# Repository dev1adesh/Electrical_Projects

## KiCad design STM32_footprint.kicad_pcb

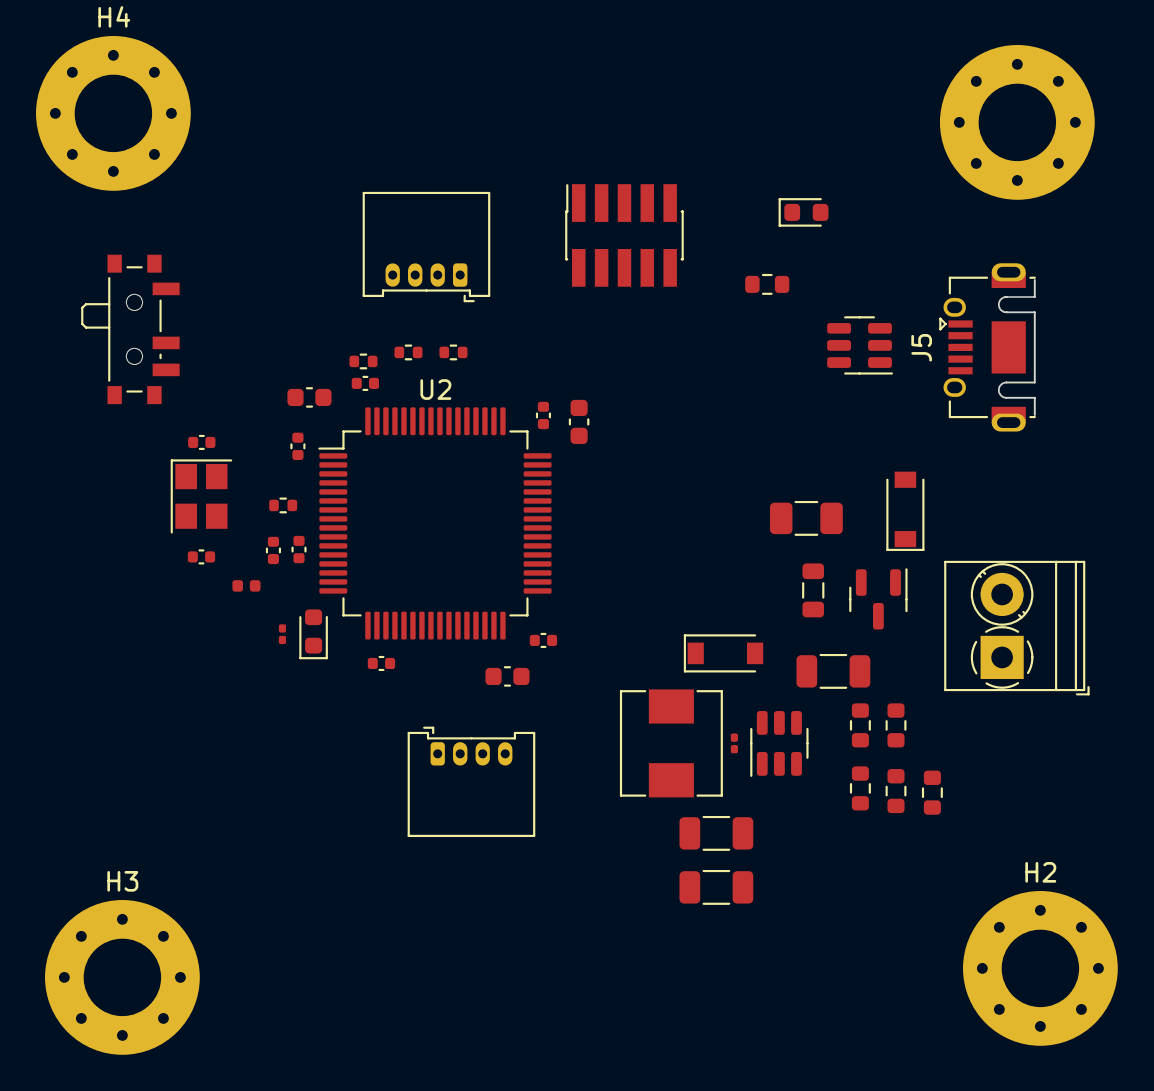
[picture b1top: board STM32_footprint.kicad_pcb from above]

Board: 4 copper layers, 50 parts (0 on the bottom side), 35 nets, no tracks yet.

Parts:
C1, C2, C3: 10u; C_1206_3216Metric
C4: 10n; C_0201_0603Metric
C5: 4u7; C_0603_1608Metric
C6, C7, C8, C9, C10: 100n; C_0402_1005Metric
C11: 1u; C_0402_1005Metric
C12: 10n; C_0402_1005Metric
C13, C14: 2u2; C_0603_1608Metric
C15, C16: 12p; C_0402_1005Metric
D1, D2: B5819W; D_SOD-123
D3: RED; LED_0603_1608Metric
D4: BLUE; LED_0603_1608Metric
F1: 250mA; Fuse_1206_3216Metric
FB1: 600 @ 600MHz; L_0805_2012Metric
H1, H2, H3, H4: MountingHole_Pad; MountingHole_4.3mm_M4_Pad_Via
J1: Screw_Terminal_01x02; TerminalBlock_Phoenix_PT-1,5-2-3.5-H_1x02_P3.50mm_Horizontal
J2: SWD; PinSocket_2x05_P1.27mm_Vertical_SMD
J3, J4: Conn_01x04; Molex_PicoBlade_53048-0410_1x04_P1.25mm_Horizontal
J5: USB_B_Micro; USB_Micro-AB_Molex_47590-0001
L1: 10u; L_Sunlord_MWSA05xxS
L2: 39n; L_0402_1005Metric
Q1: AO3401A; SOT-23
R1: 100k; R_0603_1608Metric
R2: 68k; R_0603_1608Metric
R3: 47k; R_0603_1608Metric
R4: 15k; R_0603_1608Metric
R5: 270; R_0603_1608Metric
R6: 1k; R_0603_1608Metric
R7: 10k; R_0402_1005Metric
R8: 47; R_0402_1005Metric
R9: 1k5; R_0201_0603Metric
R10, R11: 2k2; R_0402_1005Metric
SW1: SW_SPDT; SW_SPDT_PCM12
U1: MP2359DJ-LF-Z; SOT-23-6
U2: STM32F405RGT6; LQFP-64_10x10mm_P0.5mm
U3: USBLC6-2SC6; SOT-23-6
Y1: 16MHz; Crystal_SMD_3225-4Pin_3.2x2.5mm

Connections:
+3.3V: C2.1, C3.1, D3.2 (A), J2.1, J3.1, J4.1, L1.2, L2.1, R3.1, R10.1, R11.1, SW1.1 (A), U2.1 (VBAT), U2.19 (VDD), U2.32 (VDD), U2.48 (VDD), U2.64 (VDD)
+3.3VA: C5.1, C6.1, C7.1, C8.1, C9.1, C10.1, C11.1, C12.1, L2.2, U2.13 (VDDA)
+5V: D1.2 (A), J5.1 (VBUS), U3.5 (VBUS)
+12V: J1.1, Q1.3 (D)
BOOT0: R7.1, U2.60 (BOOT0)
BUCK_BST: C4.2, U1.1 (BST)
BUCK_EN: R1.2, R2.1, U1.4 (EN)
BUCK_FB: R3.2, R4.1, U1.3 (FB)
BUCK_IN: C1.1, FB1.2, R1.1, U1.5 (IN)
BUCK_SW: C4.1, D2.1 (K), L1.1, U1.6 (SW)
GND: C1.2, C2.2, C3.2, C5.2, C6.2, C7.2, C8.2, C9.2, C10.2, C11.2, C12.2, C13.2, C14.2, C15.2, C16.2, D2.2 (A), H1.1, H2.1, H3.1, H4.1, J1.2, J2.3, J2.5, J2.9, J3.4, J4.4, J5.5 (GND), Q1.1 (G), R2.2, R5.2, R6.2, R9.1, SW1.3 (C), U1.2 (GND), U2.12 (VSSA), U2.18 (VSS), U2.63 (VSS), U3.2 (GND), Y1.2, Y1.4
HSE_IN: C15.1, U2.5 (PH0), Y1.1
HSE_OUT: R8.1, U2.6 (PH1)
I2C1_SCL: J3.2, R10.2, U2.58 (PB6)
I2C1_SDA: J3.3, R11.2, U2.59 (PB7)
LED_STATUS: D4.2 (A), U2.16 (PA2)
NRST: J2.10, U2.7 (NRST)
unnamed: C13.1, U2.31 (VCAP_1)
unnamed: C14.1, U2.47 (VCAP_2)
unnamed: C16.1, R8.2, Y1.3
unnamed: D1.1 (K), F1.1, Q1.2 (S)
unnamed: D3.1 (K), R6.1
unnamed: D4.1 (K), R9.2
unnamed: F1.2, FB1.1
unnamed: R4.2, R5.1
unnamed: R7.2, SW1.2 (B)
SWCLK: J2.4, U2.49 (PA14)
SWDIO: J2.2, U2.46 (PA13)
SWO: J2.6, U2.55 (PB3)
USART3_RX: J4.3, U2.30 (PB11)
USART3_TX: J4.2, U2.29 (PB10)
USB_CONN_D+: J5.3 (D+), U3.3 (I/O2)
USB_CONN_D-: J5.2 (D-), U3.1 (I/O1)
USB_D+: U2.45 (PA12), U3.4 (I/O2)
USB_D-: U2.44 (PA11), U3.6 (I/O1)
